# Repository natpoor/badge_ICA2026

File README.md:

# badge_ICA2026
KiCAD etc files for the ICA 2026 PCB badge.
I am not entirely sure which files to place here, as I read some varying info on the web, so, best guess.

These files should get you a game-controller shaped blinking badge (four LEDs, colors/positions matching the Xbox controller), based on the ATMEGA 328PB chip. Has a Sleep button and a Mode button (to change blink patterns). Wants a 3v coin battery (2025/2032), and uses a connector off the programmer from Tag-Connect. Only has SMD components (so no THT on the back to catch on clothing, it's a badge to be worn). 

My coding is mostly Python and R scripts (linear), and I learned just before event-loop programming took hold, so my code works but I have been told it is a bit odd and there are better ways to do it. Next time!

Should have enough files for...

Badge - shape, art, components and layout (so the schematic, layout, and program files). 

BOM - Bill Of Materials (the parts to order).

Code - Arduino / C++ code (the .ino file). 

None of this would have happened without a lot of helpful people - posts to forums about schematics and code, sample working schematics (I copied the Arduino Uno schematic to start), some help from friends and relatives who know this material, and help from some people on the Arduino forum about the sleep code for the chip. 

Fall 2026 Update

While debugging the 2027 code (for the 2027 badge), we used Claude Code because some things that had worked in the 2026 code weren’t working. We discovered some errors in the 2026 code that either didn’t effect things or worked via a bit of random luck (specifically the pin assignments for the LEDs).

I can’t actually test these changes on the 2026 badges because I gave all of them away! Which was great. But the changes work well enough in the 2027 code. So I’m not updating the code for 2026, although if I ever ordered more of those badges I would and then I could test it.

LED pins should be…  
'''
const int some_led = PIN_PD0  
'''
…otherwise they aren’t quite assigned correctly except in some cases, but that’s not intentionally it’s just the two naming schemes happen to align briefly. That is, if you use the “PD0” code/location/name, you have to use “PIN_” in front of it.
  
Also, from Claude, and assuming no hallucinations, but these changes all seem to not negatively affect the 2027 board:
  
The analog comparator is never turned back on. ACSR |= (0 << ACD) does nothing. It should be...  
    ACSR &= ~(1 << ACD);  
[That’s annoying since I got that code from somewhere official looking.]
  
The brown-out detector isn't actually turned off during sleep. sleep_bod_disable() only lasts a few clock cycles before sleep has to start, and the ADC/ACSR lines in between use up that window. Use this order:  
    ADCSRA &= ~(1<<ADEN);  
    ACSR |= (1<<ACD);  
    sleep_enable();  
    sleep_bod_disable();  
    sleep_mode();  
  
Wake-up interrupt names. These work by luck. PD3 is PCINT19. Writing PCINT3 into PCMSK2 happens to set the same bit, but..  
    bitSet(PCMSK2, PCINT19)   
is clearer. 

The 328PB also has a fourth pin-change group, so the "clear all flags" line should be:  
    PCIFR = 0x0F

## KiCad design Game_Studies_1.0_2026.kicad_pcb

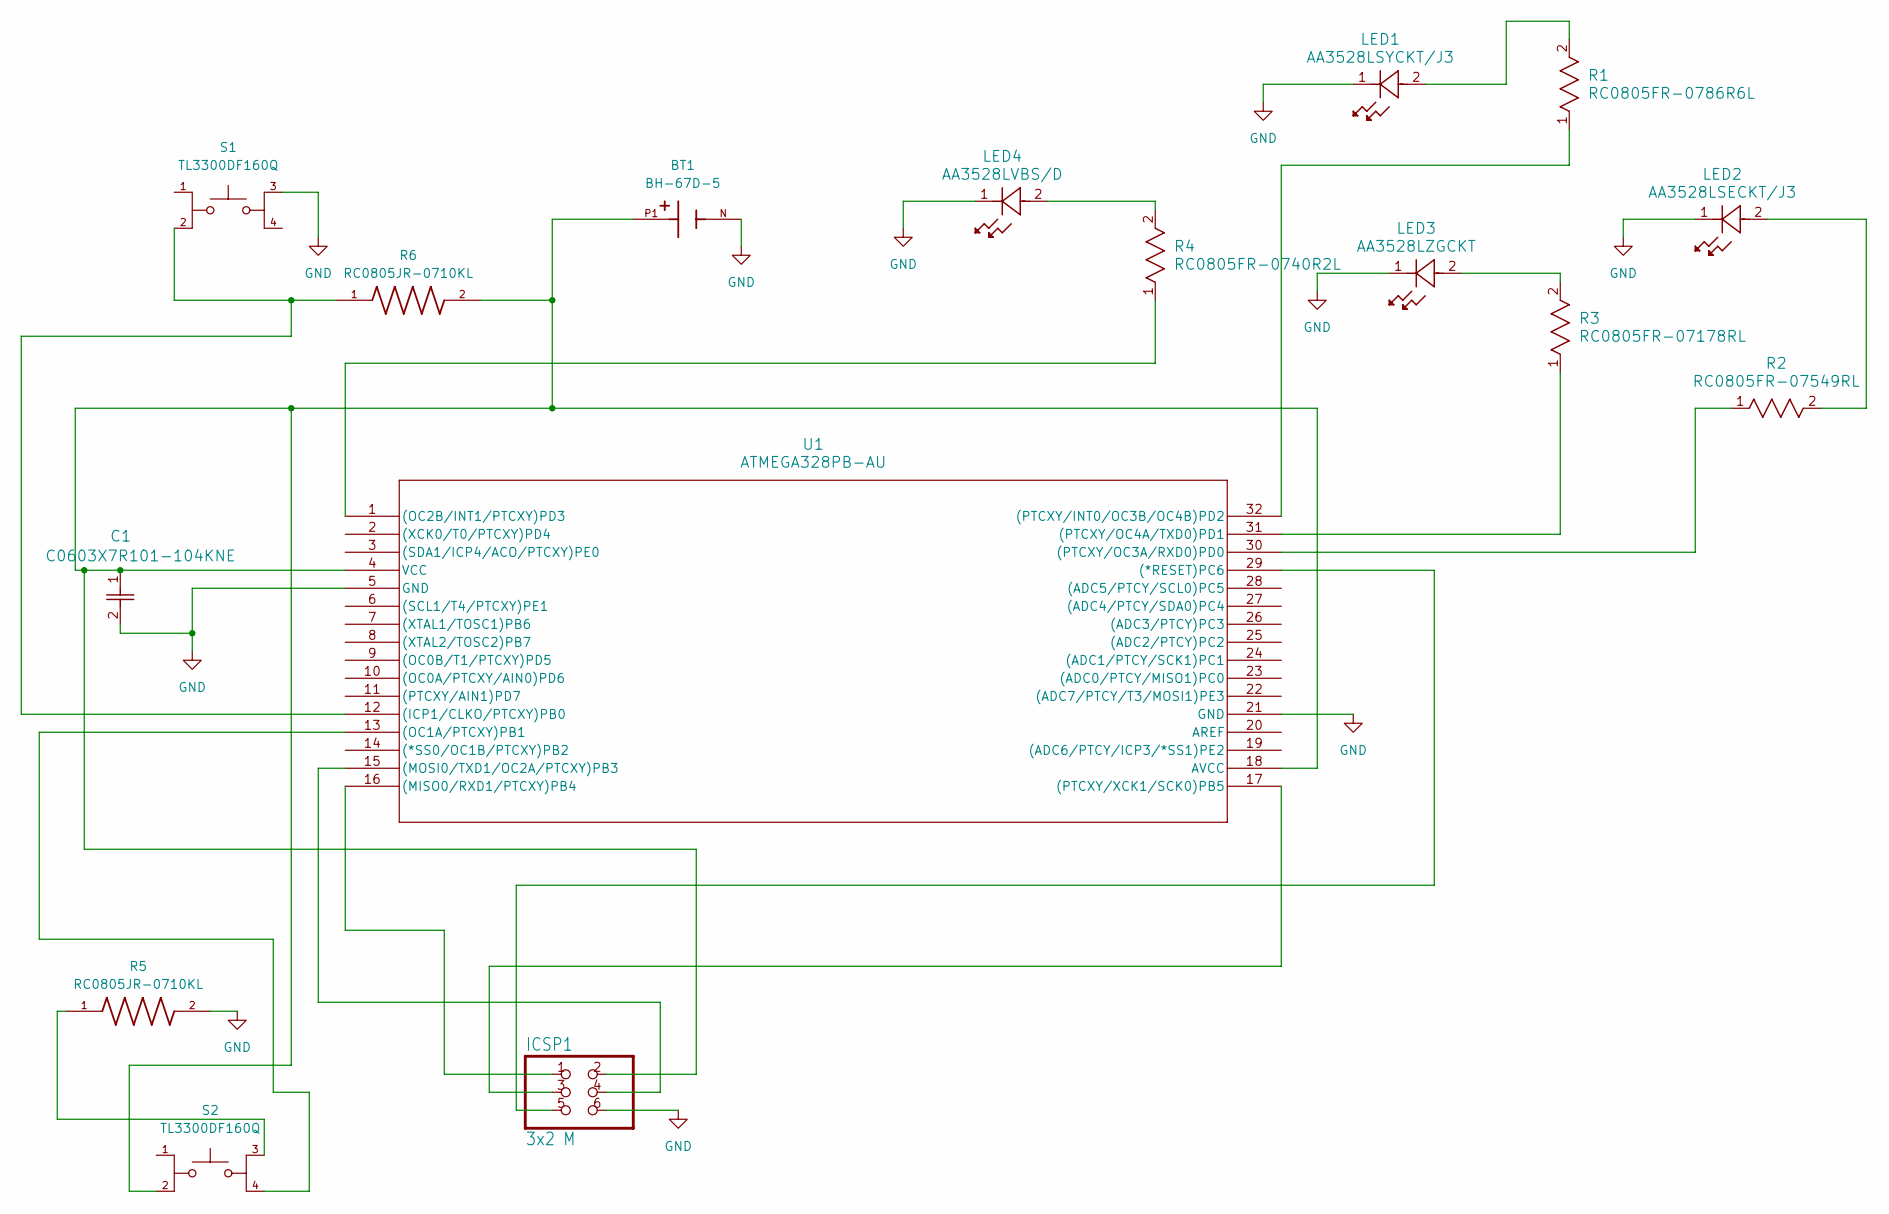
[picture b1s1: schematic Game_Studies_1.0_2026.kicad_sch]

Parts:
BT1: BH-67D-5; BAT_BH-67D-5; PARTREV A
C1: C0603X7R101-104KNE; CAP_C0603_VEN
ICSP1: 3x2 M; Conn_02x03_no_silk
LED1: AA3528LSYCKT/J3; Kingbright LED_AA3528LSYCKT&slash_J3
LED2: AA3528LSECKT/J3; Kingbright LED_AA3528LSECKT&slash_J3
LED3: AA3528LZGCKT; Kingbright LED_AA3528LZGCKT
LED4: AA3528LVBS/D; Kingbright LED_AA3528LVBS&slash_D
R1: RC0805FR-0786R6L; RC0805N_YAG
R2: RC0805FR-07549RL; RC0805N_YAG
R3: RC0805FR-07178RL; RC0805N_YAG
R4: RC0805FR-0740R2L; RC0805N_YAG
R5, R6: RC0805JR-0710KL; RESC2012X60N
S1, S2: TL3300DF160Q; SW_TL3300DF160Q; PARTREV A
U1: ATMEGA328PB-AU; 32A_MCH

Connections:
GND: BT1.N, C1.2, ICSP1.6, LED1.1, LED2.1, LED3.1, LED4.1, R5.2, S1.3, U1.5 (GND), U1.21 (GND); also elsewhere on the board
unnamed: LED1.2, R1.2
unnamed: LED2.2, R2.2
unnamed: LED3.2, R3.2
unnamed: LED4.2, R4.2
unnamed: R5.1, S2.3
unnamed: ICSP1.5, U1.29 ((*RESET)PC6)
unnamed: R6.1, S1.2, U1.12 ((ICP1/CLKO/PTCXY)PB0)
unnamed: ICSP1.1, U1.16 ((MISO0/RXD1/PTCXY)PB4)
unnamed: ICSP1.4, U1.15 ((MOSI0/TXD1/OC2A/PTCXY)PB3)
unnamed: S2.4, U1.13 ((OC1A/PTCXY)PB1)
unnamed: R4.1, U1.1 ((OC2B/INT1/PTCXY)PD3)
unnamed: R1.1, U1.32 ((PTCXY/INT0/OC3B/OC4B)PD2)
unnamed: R2.1, U1.30 ((PTCXY/OC3A/RXD0)PD0)
unnamed: R3.1, U1.31 ((PTCXY/OC4A/TXD0)PD1)
unnamed: ICSP1.3, U1.17 ((PTCXY/XCK1/SCK0)PB5)
unnamed 16: BT1.P1, C1.1, ICSP1.2, R6.2, S2.2, U1.4 (VCC), U1.18 (AVCC); also elsewhere on the board

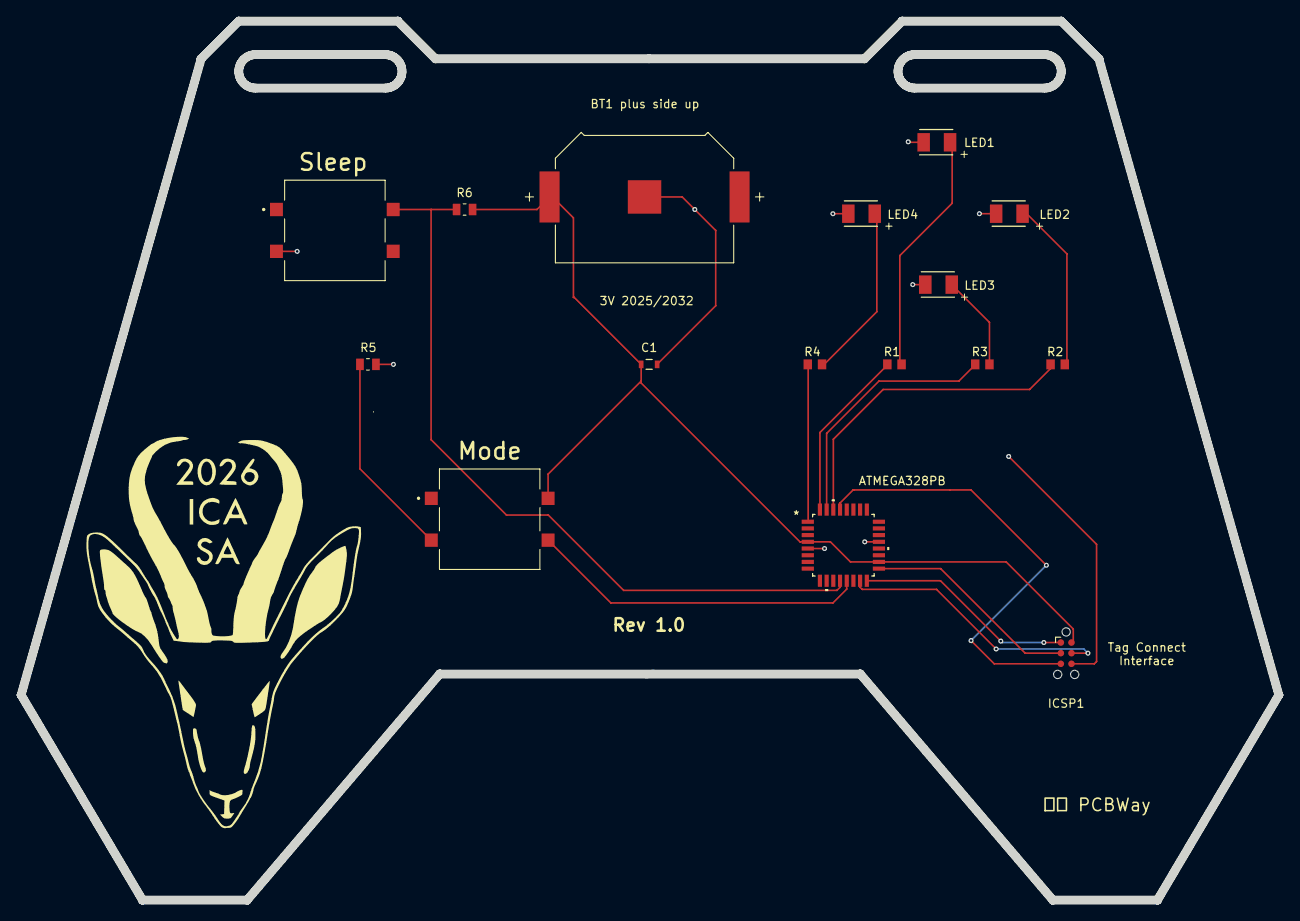
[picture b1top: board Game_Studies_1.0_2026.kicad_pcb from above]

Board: 2 copper layers, 150.3 x 105.1 mm, 16 parts (0 on the bottom side), 17 nets.

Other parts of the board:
BT1 plus side up: BH-67D-5; BAT_BH-67D-5

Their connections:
GND: BT1 plus side up.N; also elsewhere on the board
unnamed 16: BT1 plus side up.P1; also elsewhere on the board

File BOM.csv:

Item #,Designator,Component,Quantity,Manufacturer,MPN,Description,Mount Type,Notes,Notes 2,Datasheet,
1,R1,86.6 Ohm resistor,1,YAGEO,RC0805FR-0786R6L,RES 86.6 OHM 1% 1/8W 0805,SMD,Specific manufacturer not important. Selected to work with specific LED's luminosity levels.,For Yellow LED.,https://www.yageogroup.com/content/datasheet/asset/file/PYU-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,
2,R2,549 Ohm resistor,1,YAGEO,RC0805FR-07549RL,RES 549 OHM 1% 1/8W 0805,SMD,Specific manufacturer not important. Selected to work with specific LED's luminosity levels.,For Red LED.,https://www.yageogroup.com/content/datasheet/asset/file/PYU-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 ,
3,R3,178 Ohm resistor,1,YAGEO,RC0805FR-07178RL,RES 178 OHM 1% 1/8W 0805,SMD,Specific manufacturer not important. Selected to work with specific LED's luminosity levels.,For Green LED.,https://www.yageogroup.com/content/datasheet/asset/file/PYU-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 ,
4,R4,40.2 Ohm resistor,1,YAGEO,RC0805FR-0740R2L,RES 40.2 OHM 1% 1/8W 0805,SMD,Specific manufacturer not important. Selected to work with specific LED's luminosity levels.,For Blue LED.,https://www.yageogroup.com/content/datasheet/asset/file/PYU-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 ,
5,"R5,R6",10k Ohm resistors,2,YAGEO,RC0805JR-0710KL,RES 10K OHM 5% 1/8W 0805,SMD,Specific manufacturer not important.,,https://calchip.com/wp-content/uploads/2025/05/RMSERIES-052225.pdf,
6,"S1,S2",Buttons,2,E-Switch,TL3300DF160Q,SWITCH TACTILE SPST-NO 0.05A 12V,SMD,Specific manufacturer not important.,Off-mom,https://configured-product-images.s3.amazonaws.com/Datasheet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,
7,LED1,LED Yellow,1,Kingbright,AA3528LSYCKT/J3,LED YELLOW CLEAR 2SMD,SMD,Specific manufacturer not important (as long as they work with the resistors).,"1.85V, 2mA",https://www.kingbrightusa.com/images/catalog/SPEC/AA3528LSYC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,
8,LED2,LED Red,1,Kingbright,AA3528LSECKT/J3,LED RED CLEAR 2SMD,SMD,Specific manufacturer not important (as long as they work with the resistors).,"1.8V, 2mA",https://www.kingbrightusa.com/images/catalog/SPEC/AA3528LSEC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,
9,LED3,LED Green,1,Kingbright,AA3528LZGCKT,LED GREEN CLEAR 2SMD,SMD,Specific manufacturer not important (as long as they work with the resistors).,"2.65V, 2mA",https://www.kingbrightusa.com/images/catalog/SPEC/AA3528LZGCKT.pdf,
10,LED4,LED Blue,1,Kingbright,AA3528LVBS/D,LED BLUE CLEAR 2SMD,SMD,Specific manufacturer not important (as long as they work with the resistors).,"2.65V, 2mA",https://www.kingbrightusa.com/images/catalog/SPEC/AA3528LVBS-D.pdf,
11,U1,ATMEGA 328PB,1,Microchip Technology,ATMEGA328PB-AU,IC MCU 8BIT 32KB FLASH 32TQFP,SMD,This is the important component (for programming).,,https://ww1.microchip.com/downloads/en/DeviceDoc/40001907A.pdf ,
12,C1,Capacitor 0.1 µF,1,Murata Power Solutions Inc.,GCM21BR72A104KA37L,CAP CER 0.1UF 100V X7R 0805,SMD,Specific manufacturer not important.,,https://search.murata.co.jp/Ceramy/image/img/A01X/G101/ENG/G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,
13,BT1,Battery Holder,1,Adam Tech,BH-67D-5,BATTERY RETAINER COIN 20MM SMD,SMD,"Specific manufacturer not important. Please make sure the battery insertion side is facing up towards the near edge of the board, not down (because then the capacitor is in the way). Yes solder paste on the middle tab (I have tried to indicate this in the PCB but I think I have not done it correctly.)",,https://app.adam-tech.com/products/download/data_sheet/19697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 ,
-,ICSP1,Surface Pads,(1),Tag Connect,(for the TC2030-IDC-NL),Surface Pads and Holes (pads-only ICSP),(DNP),DNP,This is just the pads and holes on the PCB. No part to order.,https://www.tag-connect.com/wp-content/uploads/bsk-pdf-manag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 ,
